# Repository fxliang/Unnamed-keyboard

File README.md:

The Unnamed Keyboard is a 42-key, diodeless, flippable, low profile choc v1 or MX 3 pin switch hotswap, IO protected, aggressive column staggered, programmable ergonomic mechnical split keyboard powered by Rasyberry Pi Pico or other compatible RP2040 boards. It is based on the [Piantor](https://github.com/beekeeb/piantor) Keyboard. 
## Features

* Powered by RP2040 MCU with Raspberry Pi Pico
* Cantor & Corne like layout
* Flippable layout
* Diodeless
* Split hand pin for automatically left hand detection, single firmware for both sides
* TRRS with resistor protection, hot-plug no damage 
* Hybrid hotswap: low profile choc switches and MX switches(3pin)

## BOM
* Raspberry Pi Pico (or compatible one) * 2
* choc swtiches / MX(3pin) switches * 42
* hotswap sockets for choc swtiches / MX(3pin) switches * 42
* TRRS sockets * 2, C128990(JLC),or PJ-393-7P in tb.
* 3.5mm TRRS wire (4 pin)
* 100r 0805 resistor * 4 (for io protection)
* 1k 0805 resistor *  2 (for hand pin detection)

## Images
top left

bottom left(ignore the TRRS connector and pico:)

pcb top

pcb bottom

first made

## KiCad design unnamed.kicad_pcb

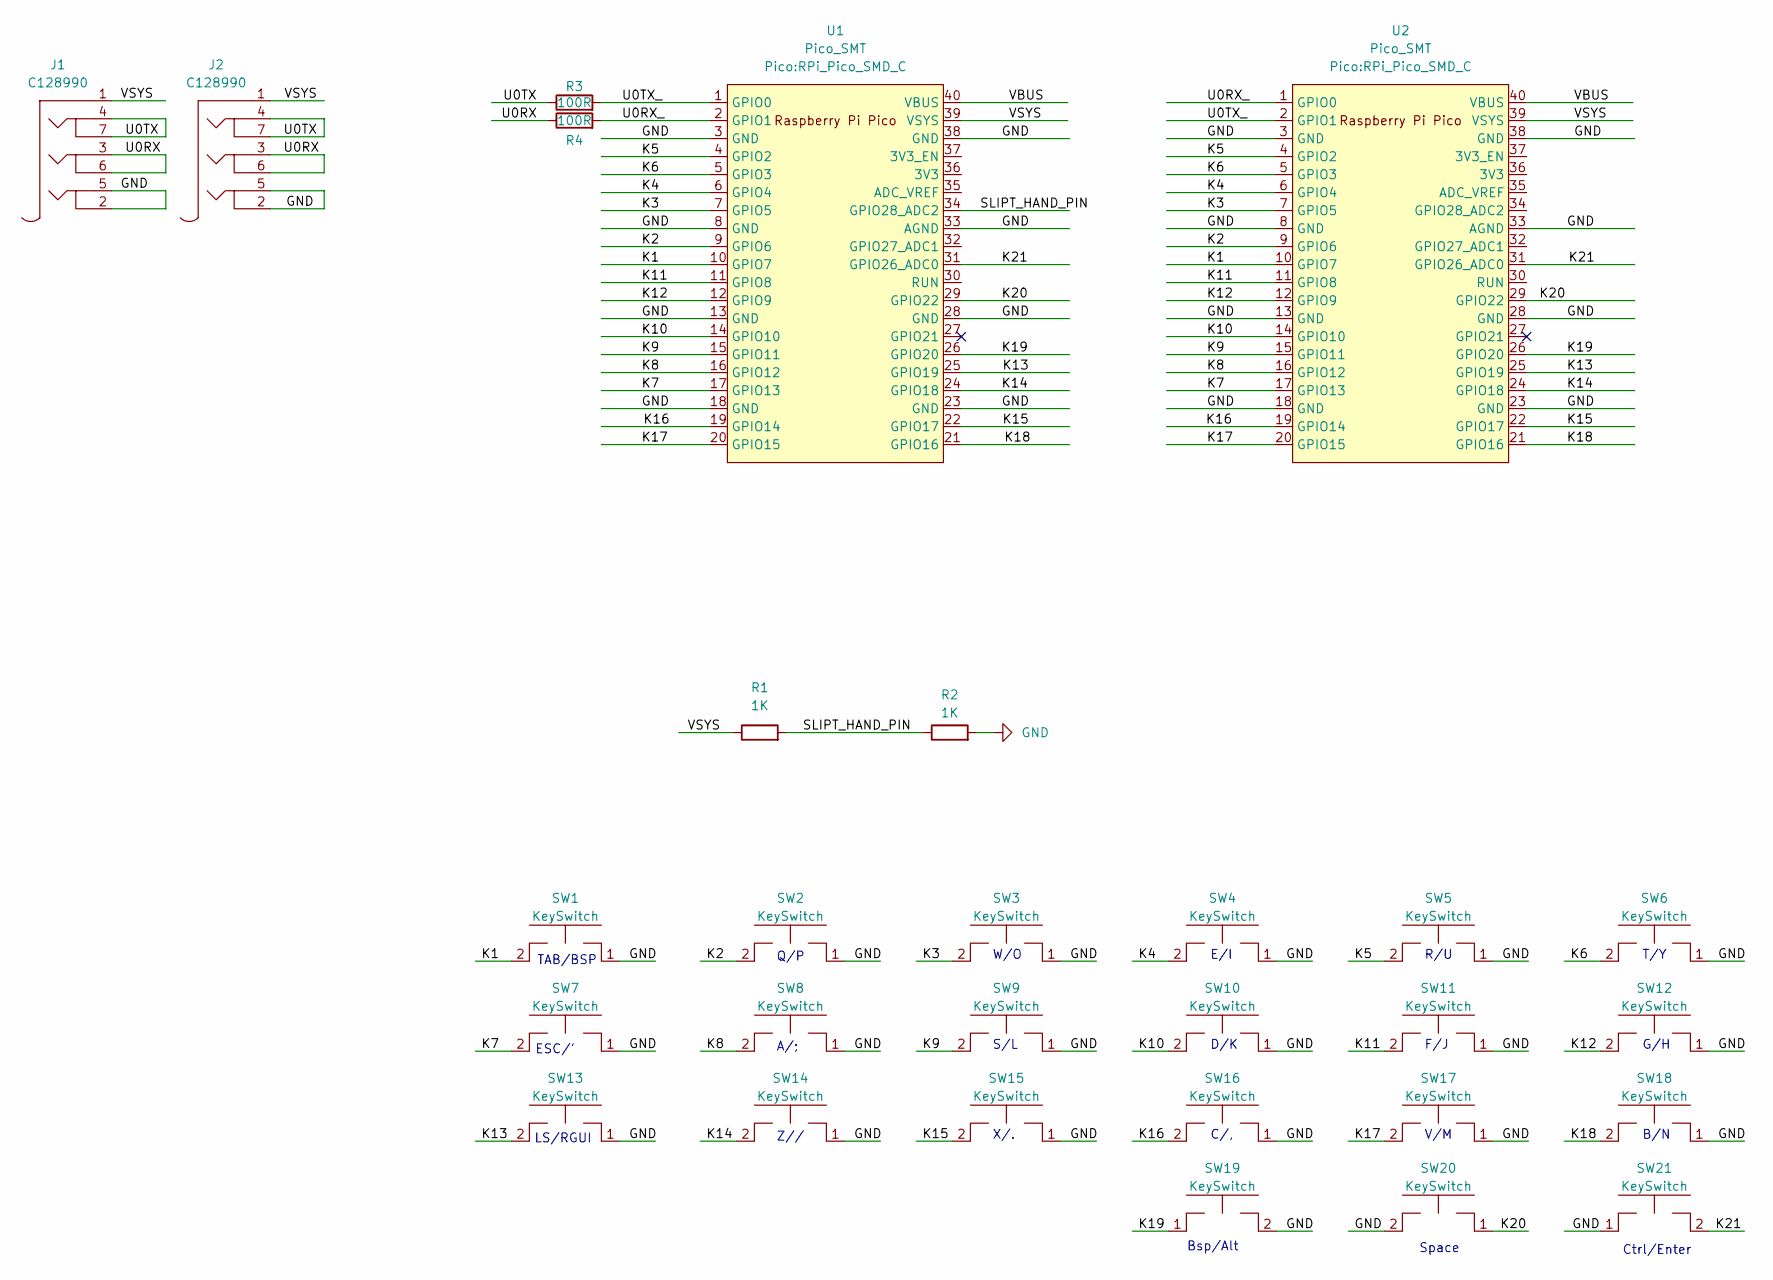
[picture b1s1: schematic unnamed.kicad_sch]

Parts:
J1, J2: C128990; C128990_3.5MM_TRRS
R1, R2: 1K; R_0805_2012Metric_Pad1.20x1.40mm_HandSolder
R3, R4: 100R; R_0805_2012Metric_Pad1.20x1.40mm_HandSolder
SW1, SW2, SW3, SW4, SW5, SW6, SW7, SW8, SW9, SW10, SW11, SW12, SW13, SW14, SW15, SW16, SW17, SW18, SW19, SW20, SW21: KeySwitch; SW_Hotswap_Kailh_Choc_V1_MX_COMBO
U1, U2: Pico_SMT; RPi_Pico_SMD_C

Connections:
/K1: SW1.2, U1.10 (GPIO7), U2.10 (GPIO7)
/K2: SW2.2, U1.9 (GPIO6), U2.9 (GPIO6)
/K3: SW3.2, U1.7 (GPIO5), U2.7 (GPIO5)
/K4: SW4.2, U1.6 (GPIO4), U2.6 (GPIO4)
/K5: SW5.2, U1.4 (GPIO2), U2.4 (GPIO2)
/K6: SW6.2, U1.5 (GPIO3), U2.5 (GPIO3)
/K7: SW7.2, U1.17 (GPIO13), U2.17 (GPIO13)
/K8: SW8.2, U1.16 (GPIO12), U2.16 (GPIO12)
/K9: SW9.2, U1.15 (GPIO11), U2.15 (GPIO11)
/K10: SW10.2, U1.14 (GPIO10), U2.14 (GPIO10)
/K11: SW11.2, U1.11 (GPIO8), U2.11 (GPIO8)
/K12: SW12.2, U1.12 (GPIO9), U2.12 (GPIO9)
/K13: SW13.2, U1.25 (GPIO19), U2.25 (GPIO19)
/K14: SW14.2, U1.24 (GPIO18), U2.24 (GPIO18)
/K15: SW15.2, U1.22 (GPIO17), U2.22 (GPIO17)
/K16: SW16.2, U1.19 (GPIO14), U2.19 (GPIO14)
/K17: SW17.2, U1.20 (GPIO15), U2.20 (GPIO15)
/K18: SW18.2, U1.21 (GPIO16), U2.21 (GPIO16)
/K19: SW19.1, U1.26 (GPIO20), U2.26 (GPIO20)
/K20: SW20.1, U1.29 (GPIO22), U2.29 (GPIO22)
/K21: SW21.2, U1.31 (GPIO26_ADC0), U2.31 (GPIO26_ADC0)
/SLIPT_HAND_PIN: R1.2, R2.1, U1.34 (GPIO28_ADC2)
/U0RX: J1.3, J1.6, J2.3, J2.6, R4.1
/U0RX_: R4.2, U1.2 (GPIO1), U2.1 (GPIO0)
/U0TX: J1.4, J1.7, J2.4, J2.7, R3.1
/U0TX_: R3.2, U1.1 (GPIO0), U2.2 (GPIO1)
/VBUS: U1.40 (VBUS), U2.40 (VBUS)
/VSYS: J1.1, J2.1, R1.1, U1.39 (VSYS), U2.39 (VSYS)
GND: J1.2, J1.5, J2.2, J2.5, R2.2, SW1.1, SW2.1, SW3.1, SW4.1, SW5.1, SW6.1, SW7.1, SW8.1, SW9.1, SW10.1, SW11.1, SW12.1, SW13.1, SW14.1, SW15.1, SW16.1, SW17.1, SW18.1, SW19.2, SW20.2, SW21.1, U1.3 (GND), U1.8 (GND), U1.13 (GND), U1.18 (GND), U1.23 (GND), U1.28 (GND), U1.33 (AGND), U1.38 (GND), U2.3 (GND), U2.8 (GND), U2.13 (GND), U2.18 (GND), U2.23 (GND), U2.28 (GND), U2.33 (AGND), U2.38 (GND)

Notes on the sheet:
G/H
E/I
Bsp/Alt
D/K
Z//
C/,
W/O
F/J
ESC/'
Space
R/U
Q/P
Ctrl/Enter
V/M
S/L
X/.
B/N
LS/RGUI
T/Y
A/;
TAB/BSP

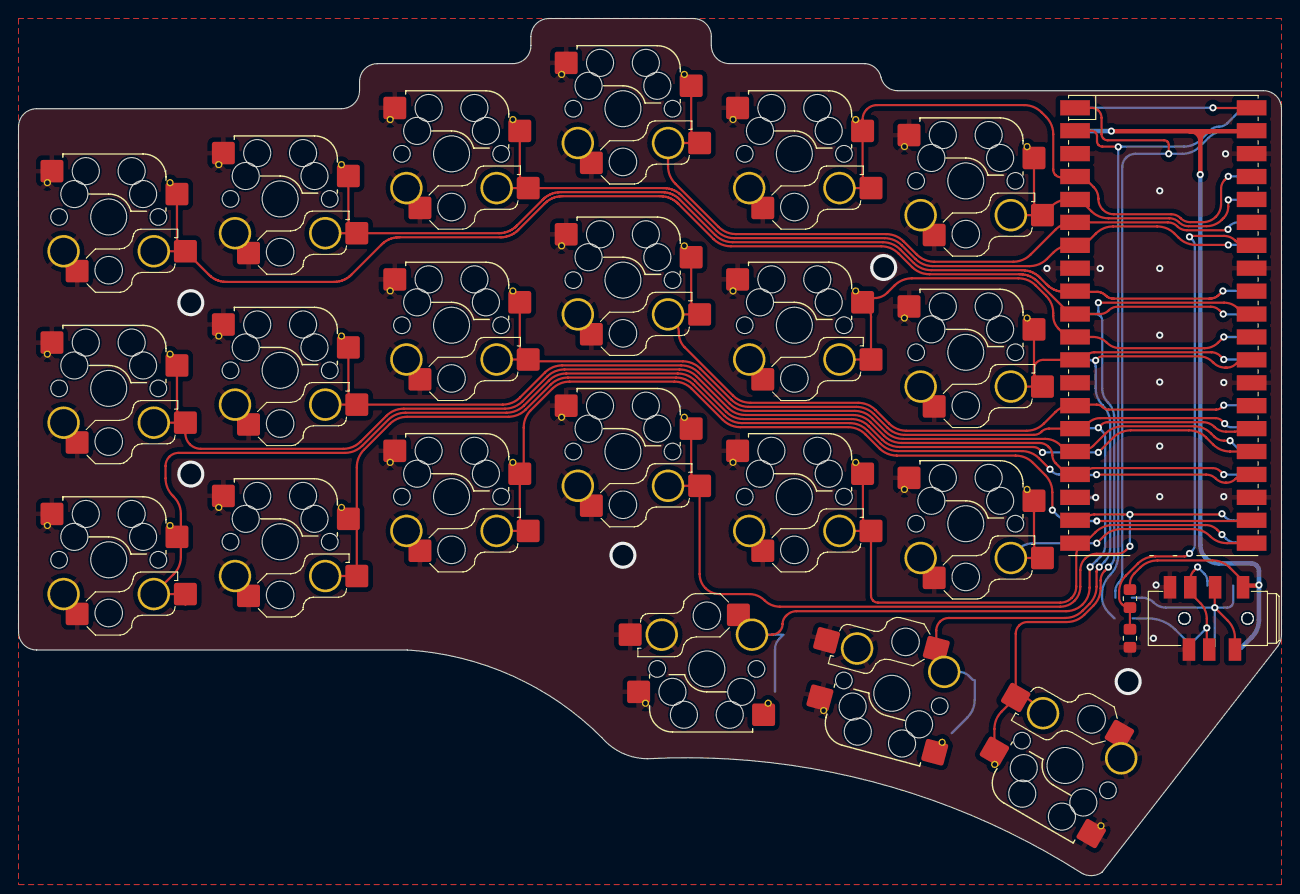
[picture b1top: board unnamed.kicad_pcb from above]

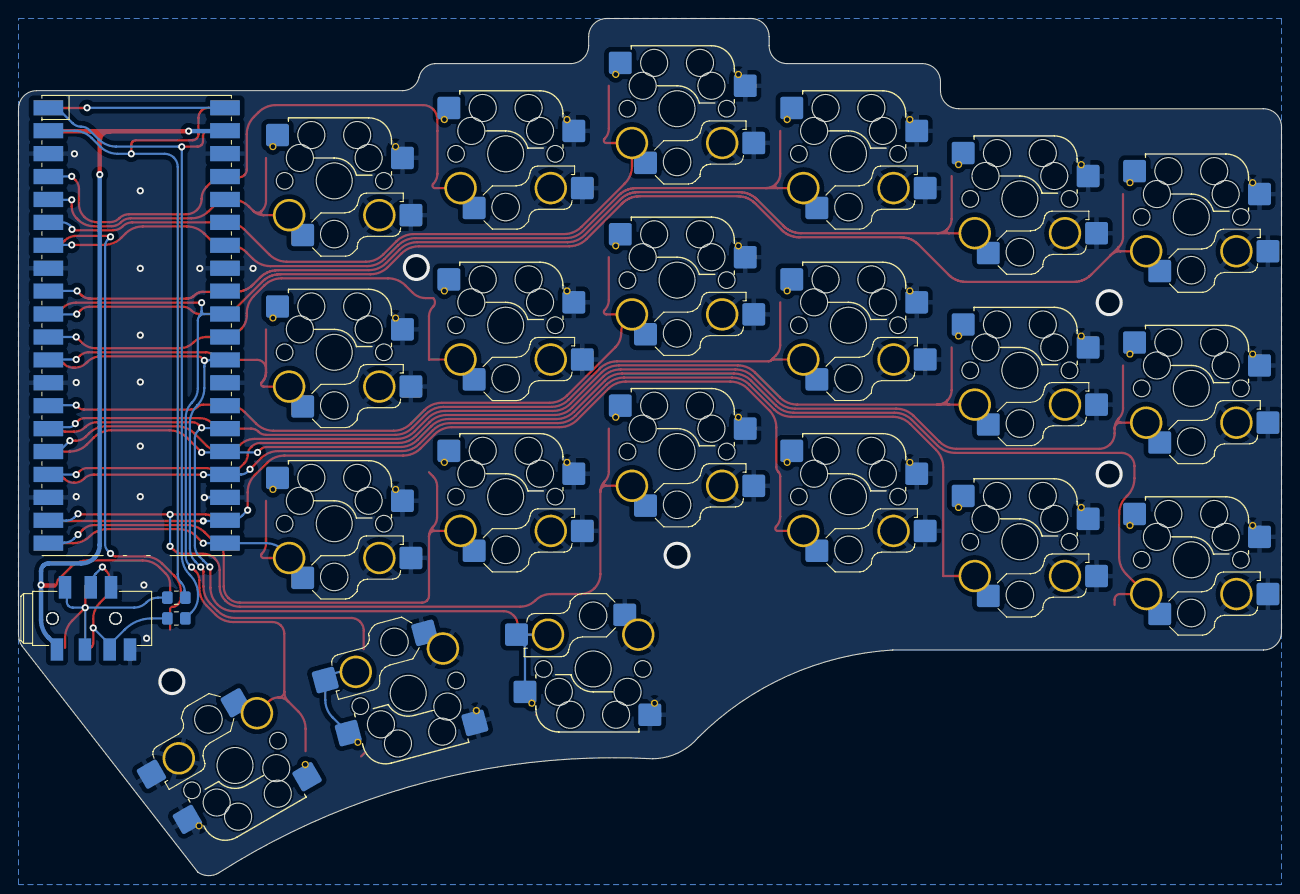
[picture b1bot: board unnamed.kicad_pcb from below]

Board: 2 copper layers, 140.0 x 95.0 mm, 29 parts (4 on the bottom side), 29 nets.

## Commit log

2023-10-30 first files commit
2023-10-31 update pcb with edge modification a little bit. add case
2023-11-01 fix drc issue
2023-11-02 update pcb and project, new 3d file for cases.
2023-11-04 add parameter info in pcb in user layer modify case model with parameters add Edge_Cuts dxf file add case.stl
2023-11-10 update footprint
2023-11-15 update switch footprint, change 0805 to hand-solder footprint, update schematic value.
2023-11-16 update key footprint, update case design(not tested yet)
2023-11-17 update pcb title, update stl file
